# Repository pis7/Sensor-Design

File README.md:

# Sensor Design Arduino Code
Contains all code related to Professor Amal El-Ghazaly's Sensor Design class labs

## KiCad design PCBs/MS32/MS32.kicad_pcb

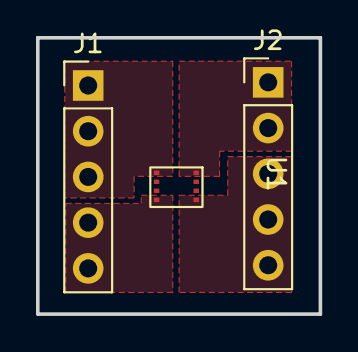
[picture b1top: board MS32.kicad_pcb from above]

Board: 2 copper layers, 15.7 x 15.4 mm, 3 parts (0 on the bottom side), 4 nets, no tracks yet.

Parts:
J1, J2: Conn_01x05; PinHeader_1x05_P2.54mm_Vertical
U1: MS32; LGA-9 3x3

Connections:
+5V: J2.3, J2.4, J2.5, U1.8 (VCC)
GND: J1.1, J1.2, J1.3, U1.4 (GND)
unnamed: J1.4, J1.5, U1.1 (+Vo)
unnamed: J2.1, J2.2, U1.5 (-Vo)

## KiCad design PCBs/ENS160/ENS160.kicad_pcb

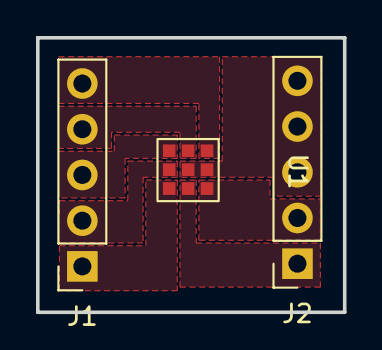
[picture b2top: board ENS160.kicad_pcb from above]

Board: 2 copper layers, 17.1 x 15.2 mm, 3 parts (0 on the bottom side), 8 nets, no tracks yet.

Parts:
J1, J2: Conn_01x05; PinSocket_1x05_P2.54mm_Vertical
U1: ENS160

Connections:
+1V8: J1.2, U1.4 (VDD)
+3V3: J1.1, U1.5 (VDDIO)
GND: J2.3, J2.4, J2.5, U1.8 (VSS), U1.9 (VSS)
unnamed: J1.3, U1.3 (MISO/ADDR)
unnamed: J1.4, U1.2 (SCLK/SCL)
unnamed: J1.5, U1.1 (MOSI/SDA)
unnamed: J2.1, U1.6 (INTn)
unnamed: J2.2, U1.7 (CSn)

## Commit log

2023-06-01 First version of Arduino and Python code
2023-06-01 Change Documentation and Fix Serial Read Bug
2023-06-30 Added bounds on serial monitor
2023-07-26 Add v1.0 of Speedometer code
2023-07-28 Add hall effect and reed switch sensing code for stealth lab
2023-08-11 8/11 Push
2023-08-14 Add 3D printed parts
2023-08-14 Rename baking lab
2023-08-14 Finalize documentation
2023-09-07 Gas lab 3D printed beaker holder changed
